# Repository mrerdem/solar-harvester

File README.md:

# Solar Harvester

Analog Devices' **ADP5092**-based solar harvester designed for **Voltaic's P121 solar panel** and **3.7 V rechargeable battery**.
It contains proper low and high-voltage cutouts to protect the battery.
If you are planning to use other than a 3.7 V battery or the preferred panel, update the resistor values for proper cutout levels (please refer to the datasheet of the IC).

The design has been tested and proven with field deployments.

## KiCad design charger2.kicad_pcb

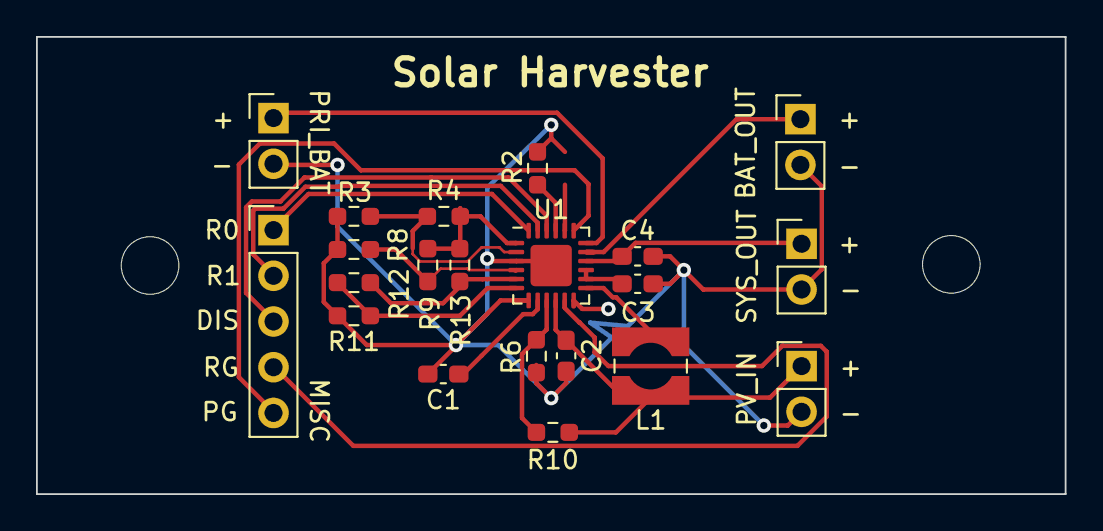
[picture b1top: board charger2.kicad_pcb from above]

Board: 2 copper layers, 57.2 x 25.4 mm, 23 parts (0 on the bottom side), 20 nets.

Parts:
C1, C2, C3, C4: CAP; C_0603_1608Metric_Pad1.08x0.95mm_HandSolder
H1, H2: MountingHole; MountingHole_3.2mm_M3
J1: PRI_BAT; PinHeader_1x02_P2.54mm_Vertical
J2: SOLAR_IN; PinHeader_1x02_P2.54mm_Vertical
J3: MISC; PinHeader_1x05_P2.54mm_Vertical
J4: BAT_OUT; PinHeader_1x02_P2.54mm_Vertical
J5: SYS_OUT; PinHeader_1x02_P2.54mm_Vertical
L1: INDUCTOR; L_Wuerth_WE-TPC-3816
R2, R3, R4, R6, R8, R9, R10, R11, R12, R13: R; R_0603_1608Metric_Pad0.98x0.95mm_HandSolder
U1: ADP5092; LFCSP-24-1EP_4x4mm_P0.5mm_EP2.3x2.3mm

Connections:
GND: C1.2, C2.2, C3.2, C4.2, J1.2, J2.2, J4.2, J5.2, R2.2, R3.2, R6.2, R8.2, R11.2, U1.3, U1.7, U1.12, U1.25
unnamed: C1.1, U1.8
unnamed: C2.1, J2.1, L1.1, R10.2, U1.10
unnamed: C3.1, U1.14, U1.15
unnamed: C4.1, J5.1, U1.16
unnamed: J1.1, U1.18
unnamed: J3.1, U1.24
unnamed: J3.2, U1.23
unnamed: J3.3, U1.22
unnamed: J3.4, U1.11
unnamed: J3.5, U1.19
unnamed: J4.1, U1.17
unnamed: L1.2, U1.13
unnamed: R2.1, U1.21
unnamed: R3.1, R4.1, U1.2
unnamed: R8.1, R9.1, U1.4
unnamed: R6.1, R10.1, U1.9
unnamed: R11.1, R12.1, U1.6
unnamed: R12.2, R13.1, U1.5
unnamed: R4.2, R9.2, R13.2, U1.1
